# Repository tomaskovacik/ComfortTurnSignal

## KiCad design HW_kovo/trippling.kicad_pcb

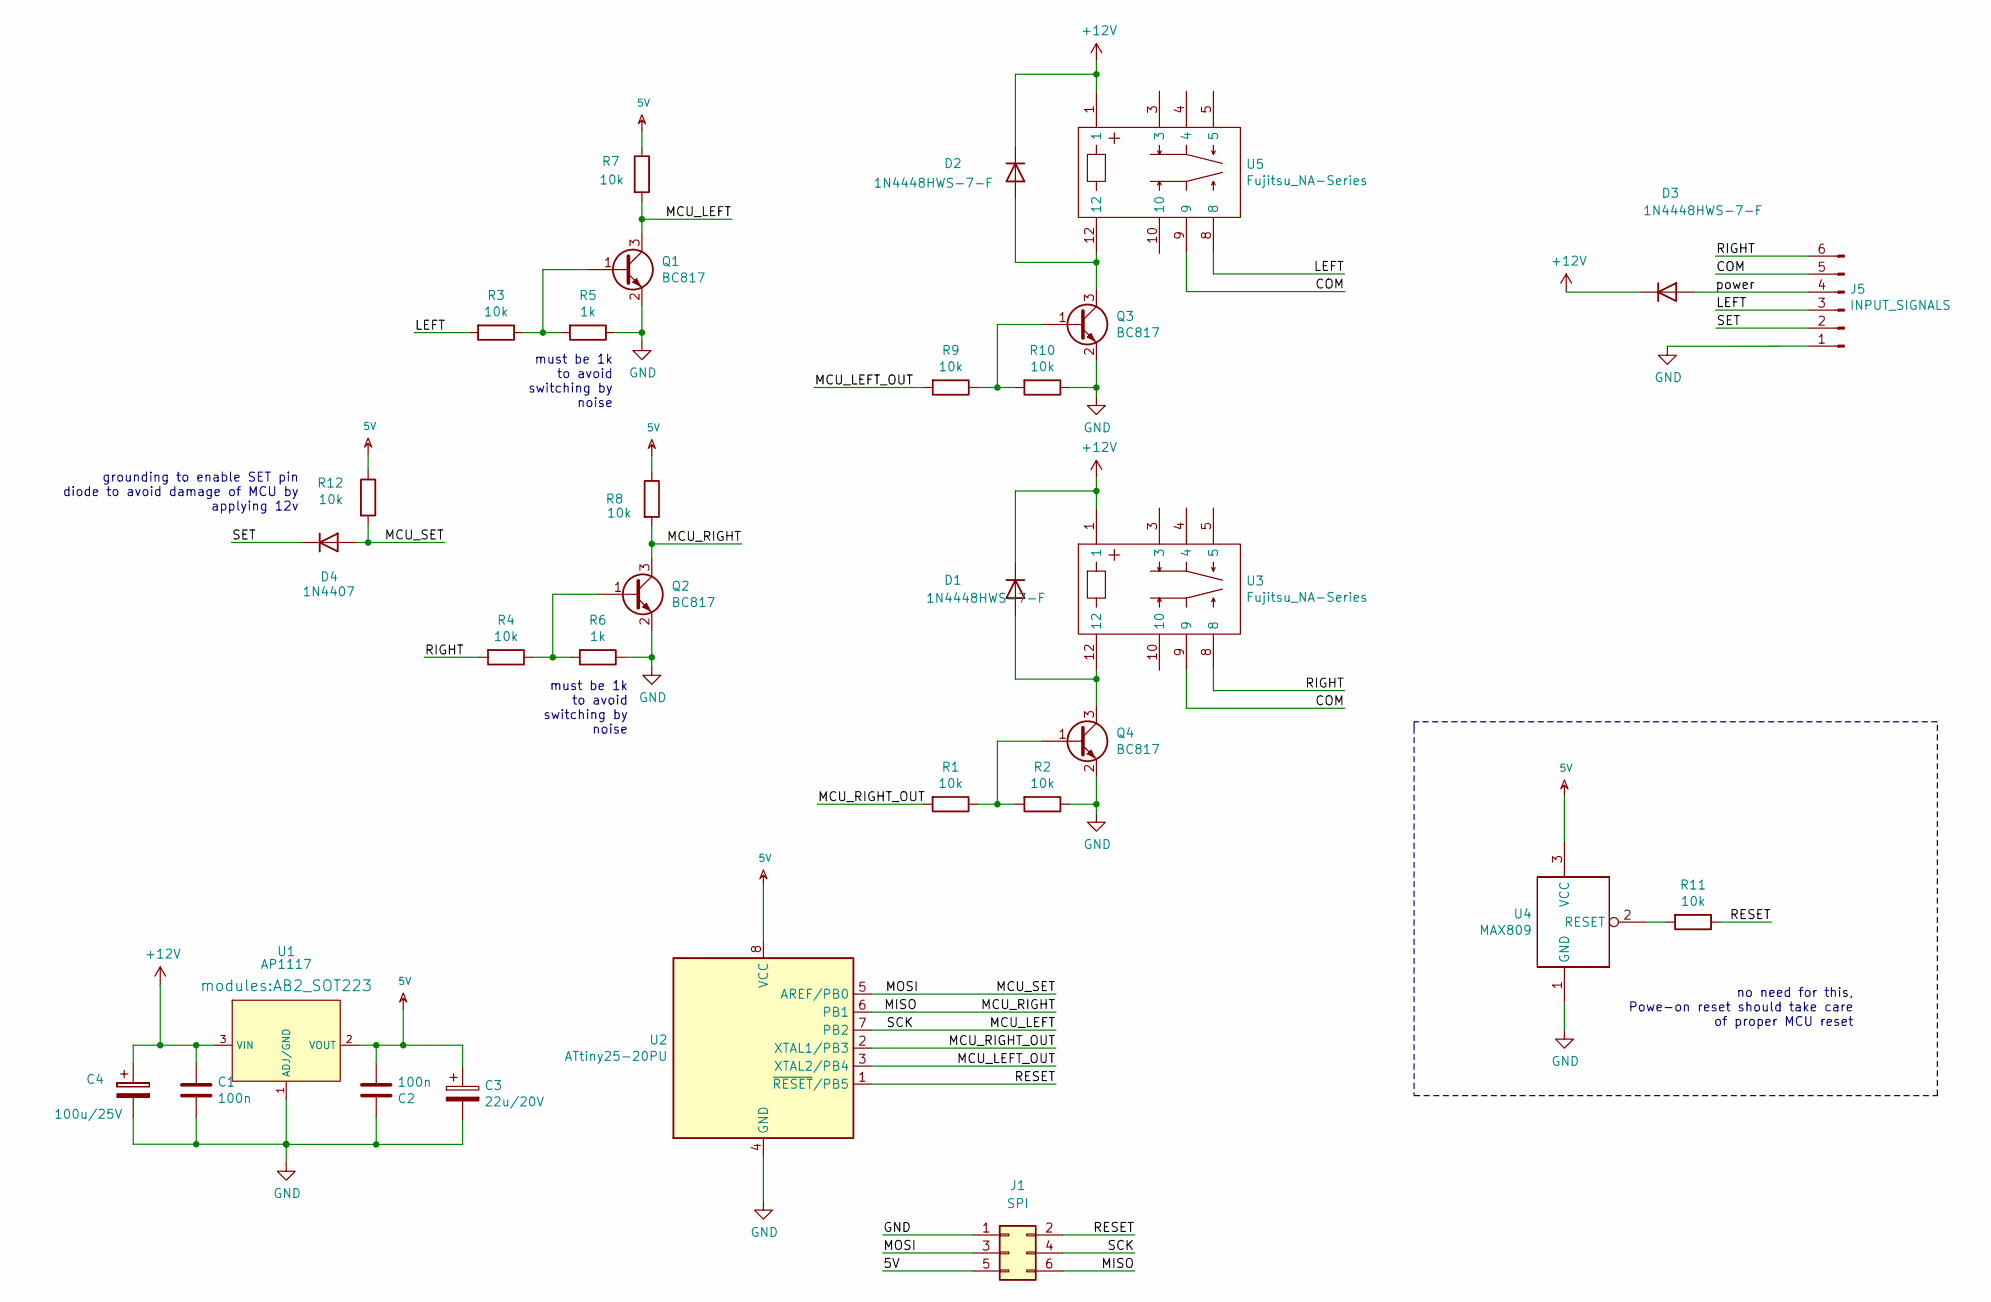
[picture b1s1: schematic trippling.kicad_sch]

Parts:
C1, C2: 100n; C_0805_HandSoldering
C3: 22u/20V; CP_Tantalum_Case-B_EIA-3528-21_Hand
C4: 100u/25V; CP_Tantalum_Case-D_EIA-7343-31_Hand
D1, D2, D3: 1N4448HWS-7-F; D_SOD-323_HandSoldering
D4: 1N4407; D_SOD-323_HandSoldering
J1: SPI; Pin_Header_Straight_2x03
J5: INPUT_SIGNALS; Molex_MiniFit-JR-5569-06A2_2x03x4.20mm_Angled
Q1, Q2, Q3, Q4: BC817; SOT-23_Handsoldering
R1, R2, R3, R4, R7, R8, R9, R10, R11, R12: 10k; R_0805_HandSoldering
R5, R6: 1k; R_0805_HandSoldering
U1: AP1117; AB2_SOT223
U2: ATtiny25-20PU; SO-8_5.3x6.2mm_Pitch1.27mm
U3, U5: Fujitsu_NA-Series; FUJITSU-NA-SERIES
U4: MAX809; SOT-23_Handsoldering

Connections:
5V: C2.2, C3.1, J1.5, R7.1, R8.1, R12.1, U1.2 (VOUT), U2.8 (VCC), U4.3 (VCC)
+12V: C1.1, C4.1, D1.1 (K), D2.1 (K), D3.1 (K), U1.3 (VIN), U3.1, U5.1
/COM: J5.5, U3.9, U5.9
/LEFT: J5.3, R3.2, U5.8
/MCU_LEFT: J1.4, Q1.3 (C), R7.2, U2.7 (PB2)
/MCU_LEFT_OUT: R9.2, U2.3 (XTAL2/PB4)
/MCU_RIGHT: J1.6, Q2.3 (C), R8.2, U2.6 (PB1)
/MCU_RIGHT_OUT: R1.2, U2.2 (XTAL1/PB3)
/MCU_SET: D4.2 (A), J1.3, R12.2, U2.5 (AREF/PB0)
/RESET: J1.2, R11.1, U2.1 (~RESET~/PB5)
/RIGHT: J5.6, R4.2, U3.8
/SET: D4.1 (K), J5.2
/power: D3.2 (A), J5.4
GND: C1.2, C2.1, C3.2, C4.2, J1.1, J5.1, Q1.2 (E), Q2.2 (E), Q3.2 (E), Q4.2 (E), R2.1, R5.1, R6.1, R10.1, U1.1 (ADJ/GND), U2.4 (GND), U4.1 (GND)
unnamed: D1.2 (A), Q4.3 (C), U3.12
unnamed: D2.2 (A), Q3.3 (C), U5.12
unnamed: Q1.1 (B), R3.1, R5.2
unnamed: Q2.1 (B), R4.1, R6.2
unnamed: Q3.1 (B), R9.1, R10.2
unnamed: Q4.1 (B), R1.1, R2.2
unnamed: R11.2, U4.2 (RESET)

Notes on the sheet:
grounding to enable SET pin diode to avoid damage of MCU by applying 12v
must be 1k to avoid switching by noise
no need for this, Powe-on reset should take care of proper MCU reset

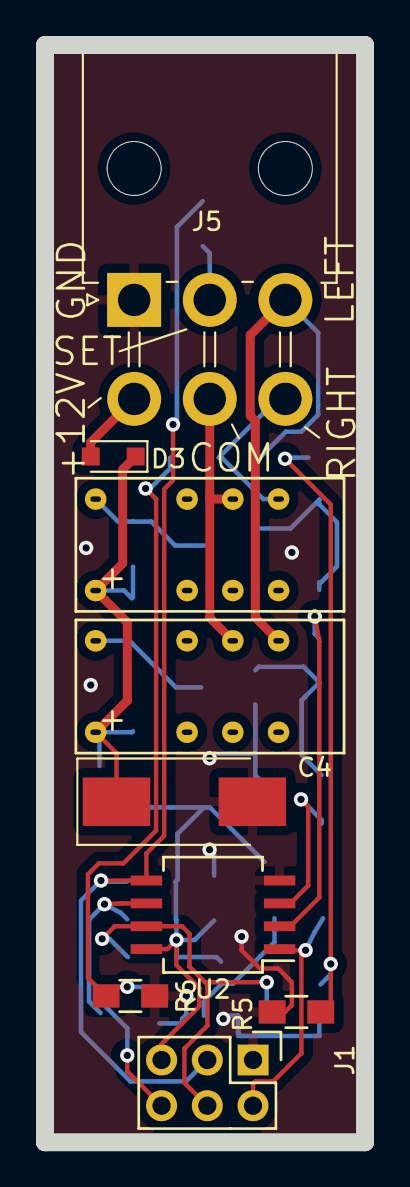
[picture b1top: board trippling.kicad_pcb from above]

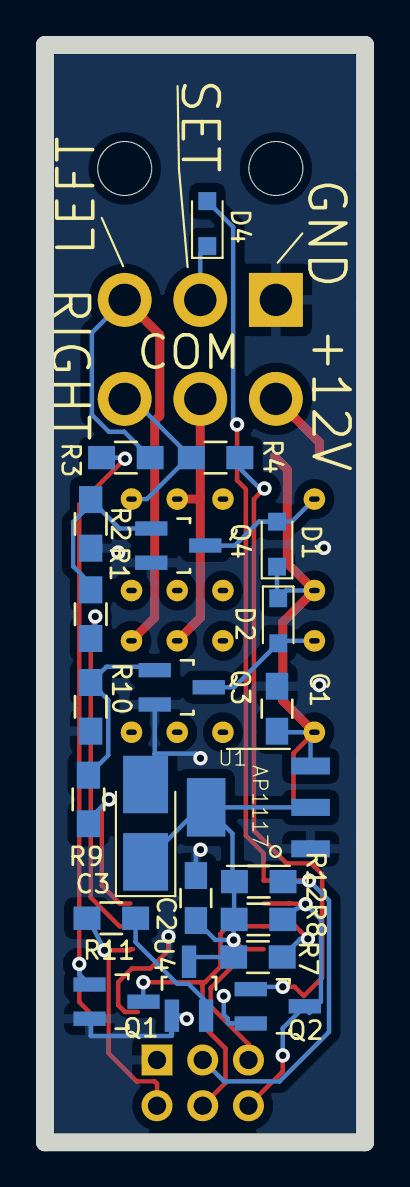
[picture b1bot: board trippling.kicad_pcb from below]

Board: 2 copper layers, 17.8 x 61.0 mm, 31 parts (22 on the bottom side), 21 nets.

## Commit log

2021-08-12 init.h -> Init.h
2021-08-12 makefile usbasp linux
2021-08-12 simple version by kovo
